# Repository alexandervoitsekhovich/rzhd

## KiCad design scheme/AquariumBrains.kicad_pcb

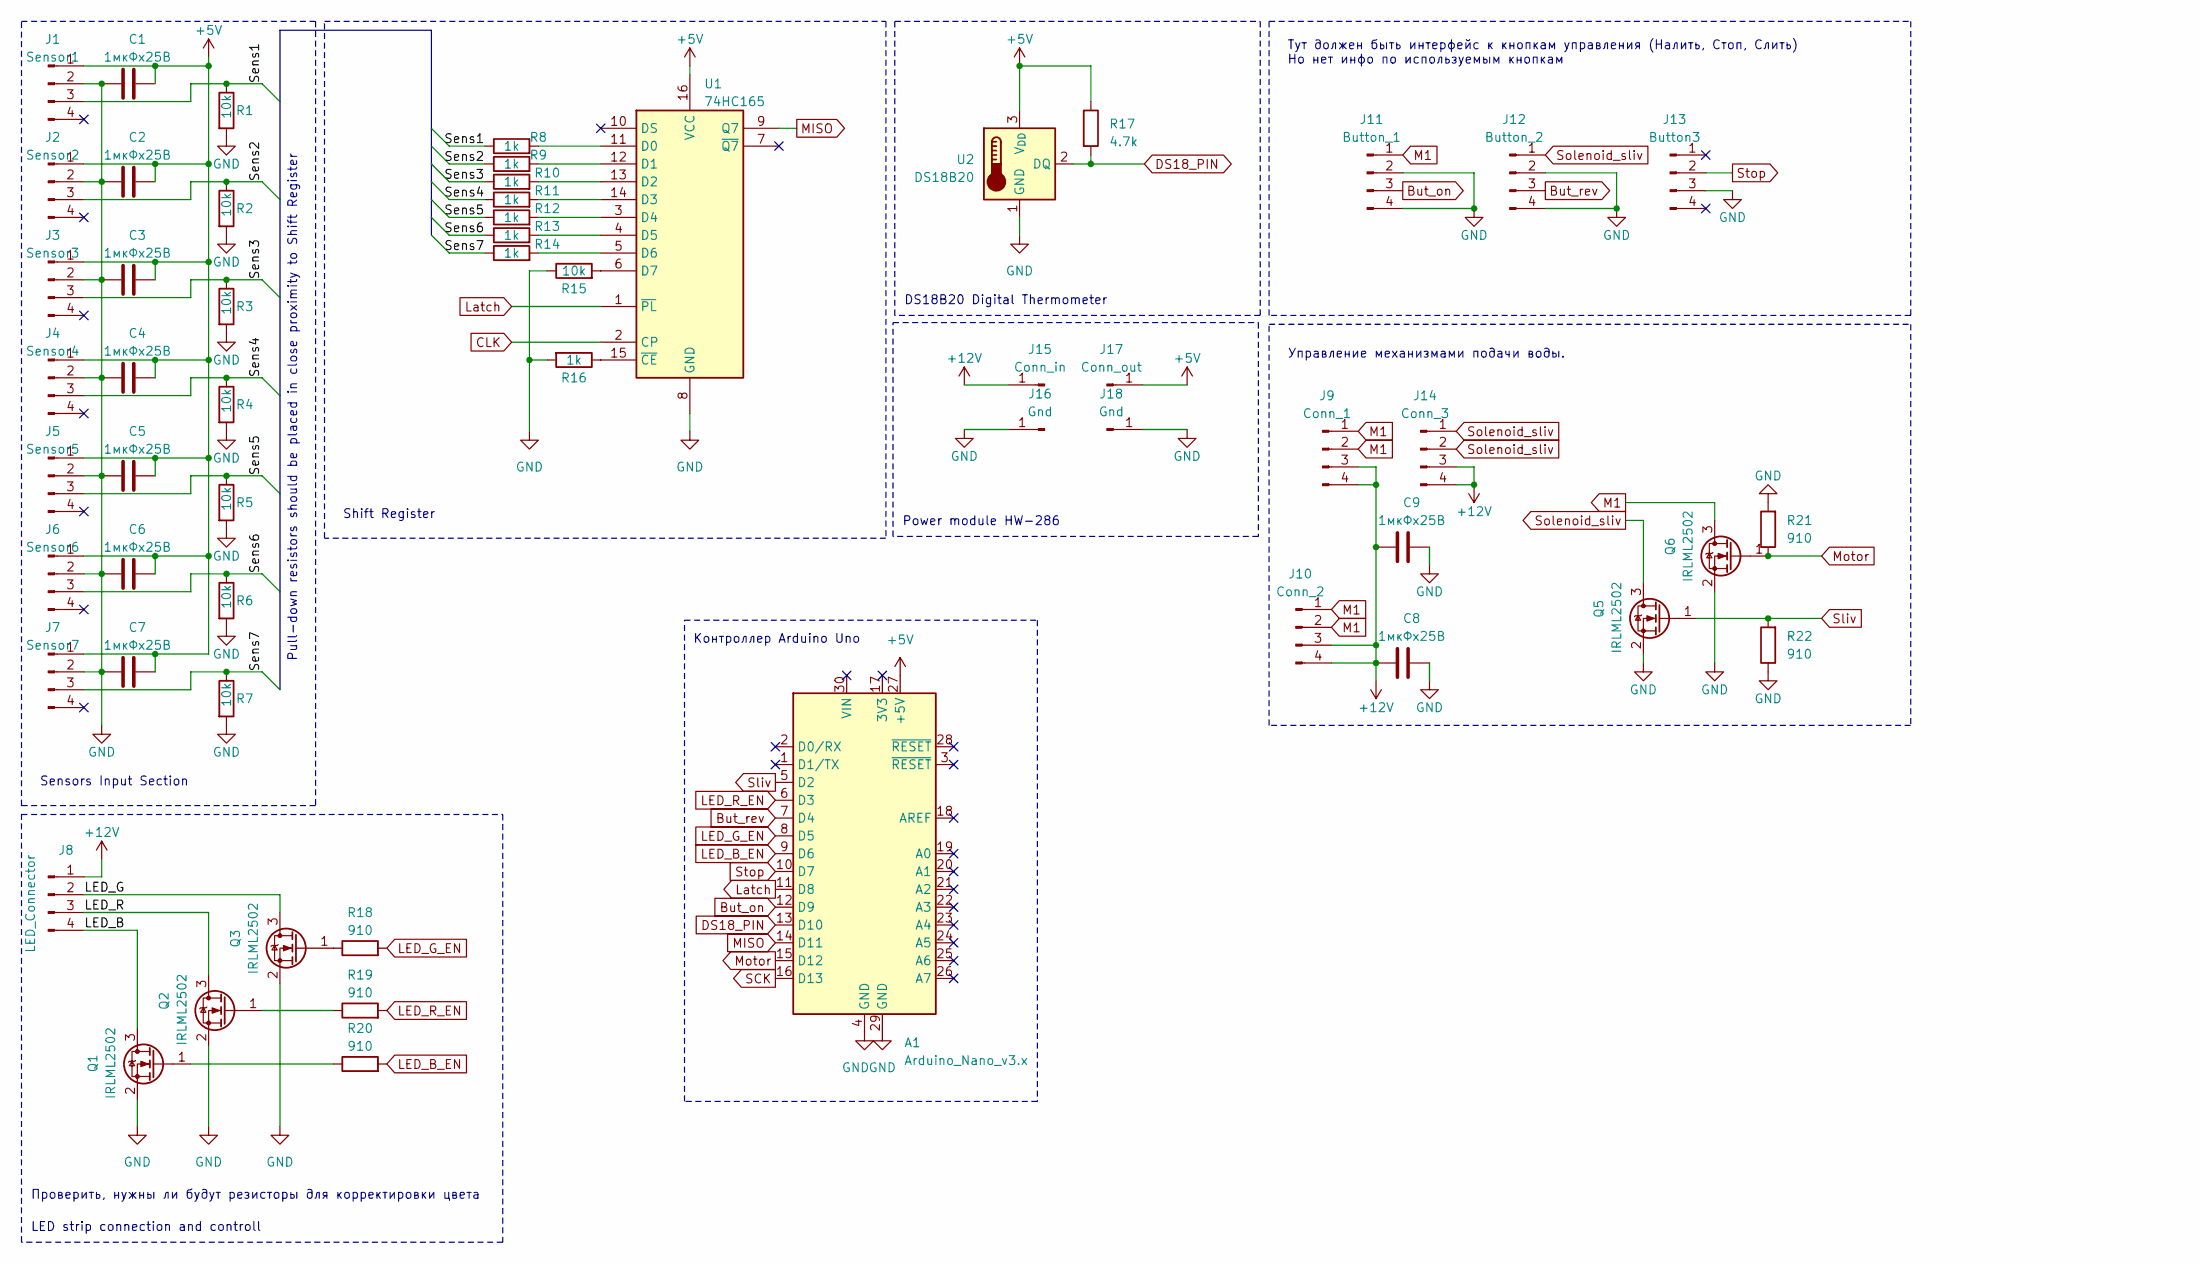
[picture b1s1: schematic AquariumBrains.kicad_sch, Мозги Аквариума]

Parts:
A1: Arduino_Nano_v3.x; Arduino_Nano
C1, C2, C3, C4, C5, C6, C7, C8, C9: 1мкФх25В; C_0805_2012Metric
J1: Sensor1; PinHeader_1x04_P2.54mm_Vertical
J2: Sensor2; PinHeader_1x04_P2.54mm_Vertical
J3: Sensor3; PinHeader_1x04_P2.54mm_Vertical
J4: Sensor4; PinHeader_1x04_P2.54mm_Vertical
J5: Sensor5; PinHeader_1x04_P2.54mm_Vertical
J6: Sensor6; PinHeader_1x04_P2.54mm_Vertical
J7: Sensor7; PinHeader_1x04_P2.54mm_Vertical
J8: LED_Connector; PinHeader_1x04_P2.54mm_Vertical
J9: Conn_1; PinHeader_1x04_P2.54mm_Vertical
J10: Conn_2; PinHeader_1x04_P2.54mm_Vertical
J11: Button_1; PinHeader_1x04_P2.54mm_Vertical
J12: Button_2; PinHeader_1x04_P2.54mm_Vertical
J13: Button3; PinHeader_1x04_P2.54mm_Vertical
J14: Conn_3; PinHeader_1x04_P2.54mm_Vertical
J15: Conn_in; PinHeader_1x01_P2.54mm_Horizontal
J16, J18: Gnd; PinHeader_1x01_P2.54mm_Horizontal
J17: Conn_out; PinHeader_1x01_P2.54mm_Horizontal
Q1, Q2, Q3, Q5, Q6: IRLML2502; SOT-23_Handsoldering
R1, R2, R3, R4, R5, R6, R7, R15: 10k; R_0805_2012Metric_Pad1.20x1.40mm_HandSolder
R8, R9, R10, R11, R12, R13, R14, R16: 1k; R_0805_2012Metric_Pad1.20x1.40mm_HandSolder
R17: 4.7k; R_0805_2012Metric_Pad1.20x1.40mm_HandSolder
R18, R19, R20, R21, R22: 910; R_0805_2012Metric_Pad1.20x1.40mm_HandSolder
U1: 74HC165; DIP-16_W7.62mm
U2: DS18B20; TO-92_Inline_Wide

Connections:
/LED_B: J8.4, Q1.3 (D)
/LED_G: J8.2, Q3.3 (D)
/LED_R: J8.3, Q2.3 (D)
/Sens1: J1.3, R1.1, R8.1
/Sens2: J2.3, R2.1, R9.1
/Sens3: J3.3, R3.1, R10.1
/Sens4: J4.3, R4.1, R11.1
/Sens5: J5.3, R5.1, R12.1
/Sens6: J6.3, R6.1, R13.1
/Sens7: J7.3, R7.1, R14.1
But_on: A1.12 (D9), J11.3
But_rev: A1.7 (D4), J12.3
CLK: U1.2 (CP)
DS18_PIN: A1.13 (D10), R17.2, U2.2 (DQ)
GND: A1.4 (GND), A1.29 (GND), C1.1, C2.1, C3.1, C4.1, C5.1, C6.1, C7.1, C8.2, C9.2, J1.2, J2.2, J3.2, J4.2, J5.2, J6.2, J7.2, J11.2, J11.4, J12.2, J12.4, J13.3, J16.1, J18.1, Q1.2 (S), Q2.2 (S), Q3.2 (S), Q5.2 (S), Q6.2 (S), R1.2, R2.2, R3.2, R4.2, R5.2, R6.2, R7.2, R15.1, R16.2, R21.2, R22.1, U1.8 (GND), U2.1 (GND); also elsewhere on the board
LED_B_EN: A1.9 (D6), R20.2
LED_G_EN: A1.8 (D5), R18.2
LED_R_EN: A1.6 (D3), R19.2
Latch: A1.11 (D8), U1.1 (~PL)
M1: J9.1, J9.2, J10.1, J10.2, J11.1, Q6.3 (D)
MISO: A1.14 (D11), U1.9 (Q7)
Motor: A1.15 (D12), Q6.1 (G), R21.1
unnamed: Q1.1 (G), R20.1
unnamed: Q2.1 (G), R19.1
unnamed: Q3.1 (G), R18.1
unnamed: R8.2, U1.11 (D0)
unnamed: R9.2, U1.12 (D1)
unnamed: R10.2, U1.13 (D2)
unnamed: R11.2, U1.14 (D3)
unnamed: R12.2, U1.3 (D4)
unnamed: R13.2, U1.4 (D5)
unnamed: R14.2, U1.5 (D6)
unnamed: R15.2, U1.6 (D7)
unnamed: R16.1, U1.15 (~CE)
SCK: A1.16 (D13)
Sliv: A1.5 (D2), Q5.1 (G), R22.2
Solenoid_sliv: J12.1, J14.1, J14.2, Q5.3 (D)
Stop: A1.10 (D7), J13.2

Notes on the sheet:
LED strip connection and controll
Pull-down resistors should be placed in close proximity to Shift Register
DS18B20 Digital Thermometer
Power module HW-286
Управление механизмами подачи воды.
Sensors Input Section
Проверить, нужны ли будут резисторы для корректировки цвета
Shift Register
Контроллер Arduino Uno
Тут должен быть интерфейс к кнопкам управления (Налить, Стоп, Слить) Но нет инфо по используемым кнопкам

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
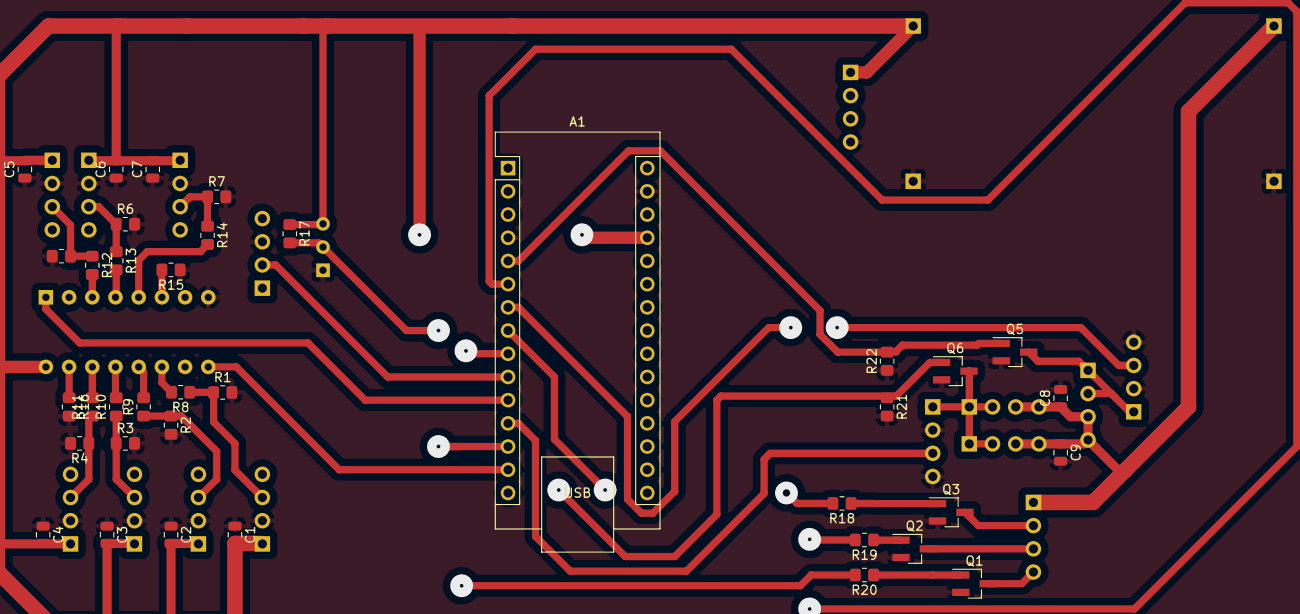
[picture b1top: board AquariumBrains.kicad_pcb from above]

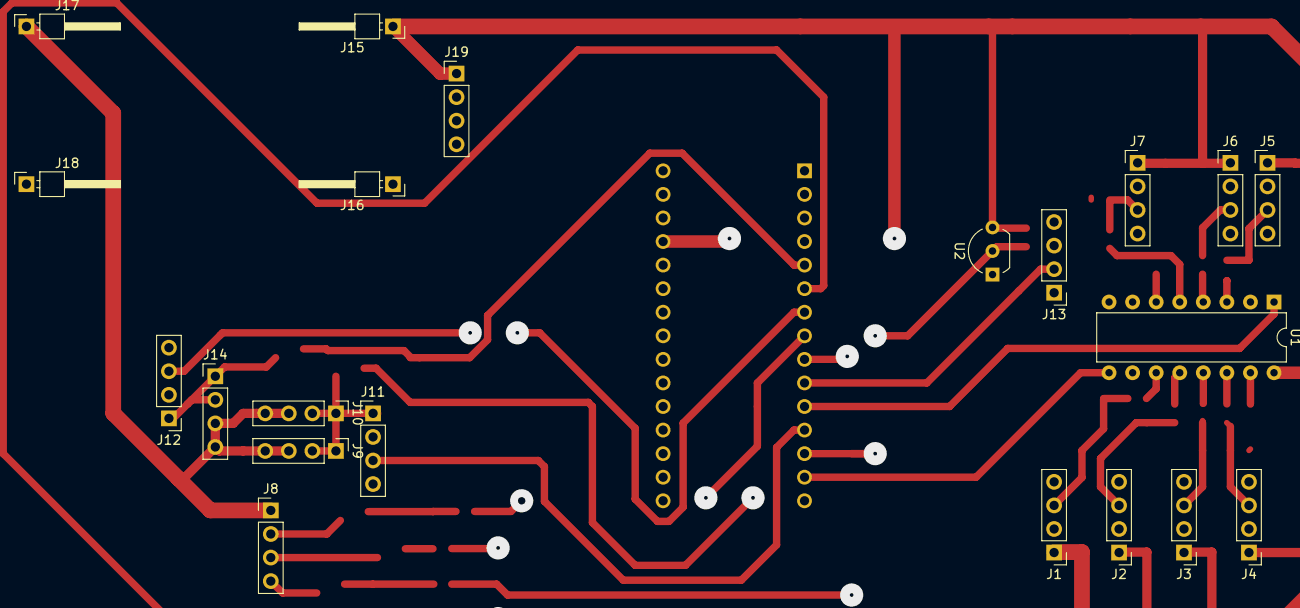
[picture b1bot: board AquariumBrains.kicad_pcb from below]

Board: 2 copper layers, 58 parts (21 on the bottom side), 38 nets.

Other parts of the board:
J19: USART; PinHeader_1x04_P2.54mm_Vertical

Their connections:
GND: J19.4; also elsewhere on the board

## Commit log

2024-01-22 updated printed circuit board
2024-01-24 pcb done
2024-01-24 Rename scheme folder
2024-01-24 Rename report.txt to report.txt
2024-01-24 Update and rename fp-lib-table to fp-lib-table
2024-01-24 Update and rename fp-info-cache to fp-info-cache
2024-01-24 Rename AquariumBrains.kicad_pro to AquariumBrains.kicad_pro
2024-01-24 Rename AquariumBrains.kicad_prl to AquariumBrains.kicad_prl
2024-01-24 Rename AquariumBrains-F_Mask.pdf to AquariumBrains-F_Mask.pdf
2024-01-24 pcb changed
2024-01-24 pcb improved, once again
2024-01-26 update scheme
2024-01-28 txt part done (and so do i)
2024-04-13 here we go again
2024-04-13 here we go again pt. 2
2024-10-16 farewell
